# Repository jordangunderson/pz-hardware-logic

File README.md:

# Pellet Zealot Logic Baord

Electronics Design -- schematic and PCB layout -- for Pellet Zealot.

KiCad v5.1.5 or later.

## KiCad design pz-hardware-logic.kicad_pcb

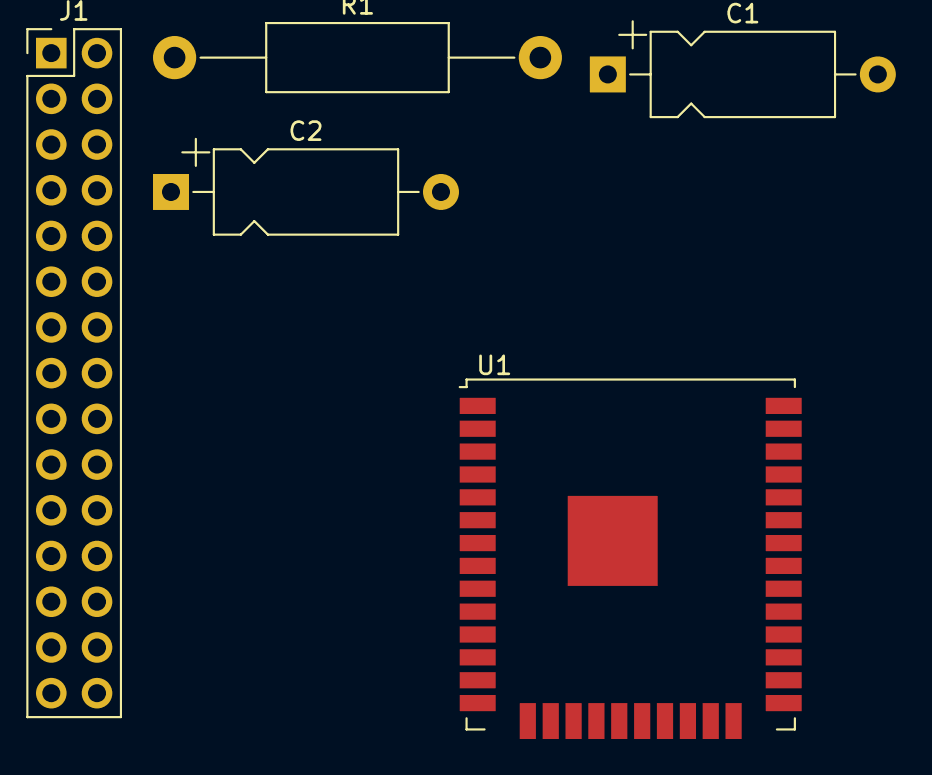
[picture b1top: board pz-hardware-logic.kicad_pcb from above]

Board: 2 copper layers, 5 parts (0 on the bottom side), 3 nets, no tracks yet.

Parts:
C1: 10uF; CP_Axial_L10.0mm_D4.5mm_P15.00mm_Horizontal
C2: 1uF; CP_Axial_L10.0mm_D4.5mm_P15.00mm_Horizontal
J1: Logic Header; PinHeader_2x15_P2.54mm_Vertical
R1: 10k; R_Axial_DIN0411_L9.9mm_D3.6mm_P20.32mm_Horizontal
U1: ESP32-WROOM-32U

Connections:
+3V3: C1.1, R1.1, U1.2
/RESET: C2.1, R1.2, U1.3
GND: C1.2, C2.2, U1.1, U1.15, U1.38, U1.39

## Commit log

2019-12-14 Initial commit.
2019-12-14 Setting up project details.
2020-03-01 Add IC and some power filters. Started reset network.

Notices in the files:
pz-hardware-logic.kicad_pcb:
Licensed under the Apache License, Version 2.0.
